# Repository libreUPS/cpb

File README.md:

# cpb
Communication panel board

In this repository you will find the `communication panel board` for the [libreUPS](https://github.com/libreUPS) complex.

Includes:
- can (x2)
- power bus (x2)
- LED (x3)
- button (x1)

Currently used in:
- bc1u15s

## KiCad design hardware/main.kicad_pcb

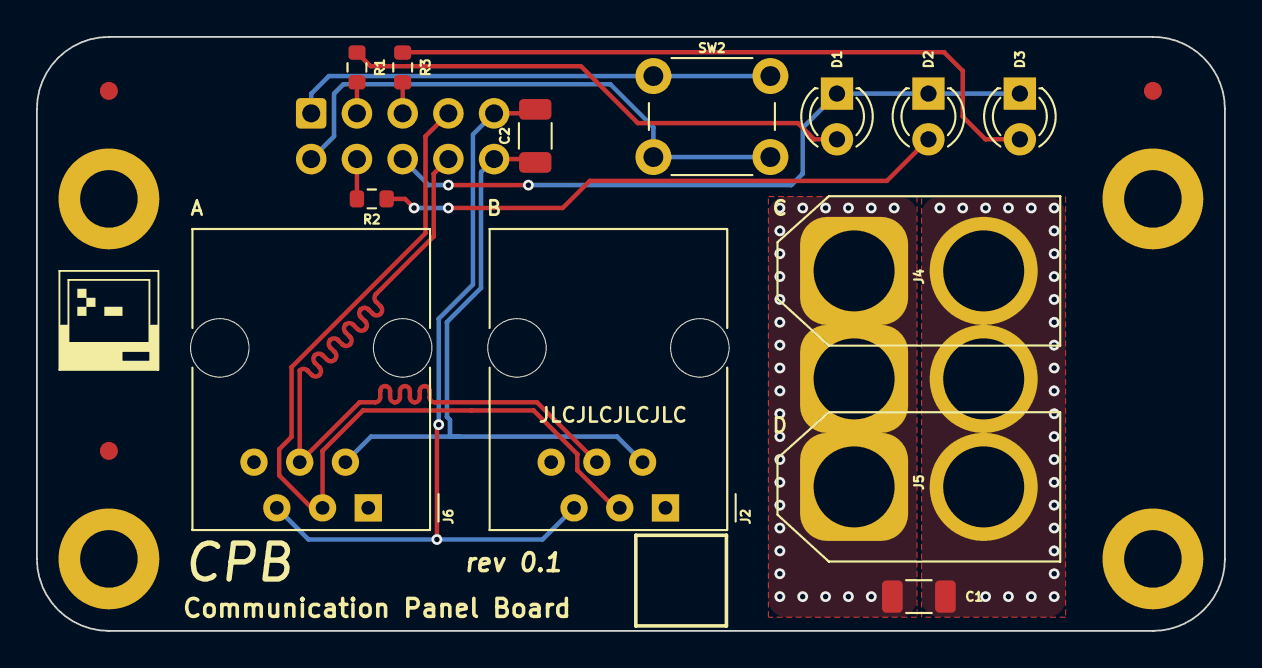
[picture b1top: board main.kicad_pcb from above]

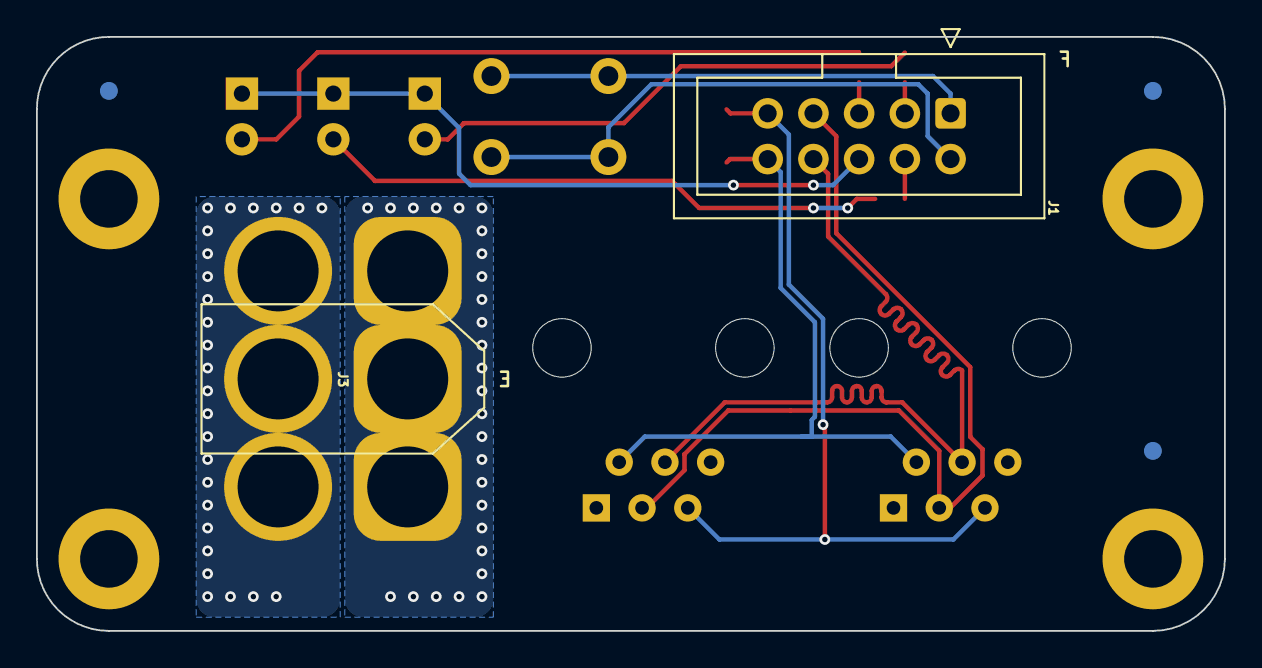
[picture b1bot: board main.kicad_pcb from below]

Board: 2 copper layers, 66.0 x 33.0 mm, 25 parts (5 on the bottom side), 15 nets.

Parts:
C1, C2: 100n; C_1206_3216Metric
D1: 204-10SUGD(E); LED_D3.0mm
D2: 204-10UYD(Y); LED_D3.0mm
D3: 204-10SURD(R); LED_D3.0mm
FID1, FID2, FID3, FID4, FID5, FID6: F; Fiducial_1mm_Mask3mm
H1, H2, H3, H4: H; MountingHole_3.2mm_M3_DIN965_Pad
J1: DS1013-10S; IDC-Header_2x05_P2.54mm_Vertical
J2, J6: KH-9752-6P6C; RJ12_Vertical
J3, J5: XT60; AMASS_XT60-F_1x02_P7.20mm_Vertical
J4: XT60; AMASS_XT60-M_1x02_P7.20mm_Vertical
R1, R2, R3: 1k; R_0603_1608Metric
SW2: TL1105HF160Q; SW_PUSH_6mm_H13mm

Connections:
/CANH: J1.7, J2.3, J6.3
/CANL: J1.8, J2.4, J6.4
/CANgnd: C2.2, J1.9, J2.5, J6.5
/CANvcc: C2.1, J1.10, J2.2, J6.2
/IO1: J1.3, R1.2
/IO2: J1.4, R2.2
/IO3: J1.5, R3.2
/K1: J1.1, SW2.1 (A)
/K2: J1.2, SW2.2 (B)
GND: D1.1 (K), D2.1 (K), D3.1 (K), J1.6
unnamed: C1.1, J3.1, J4.1, J5.1
unnamed: C1.2, J3.2, J4.2, J5.2
unnamed: D1.2 (A), R1.1
unnamed: D2.2 (A), R2.1
unnamed: D3.2 (A), R3.1

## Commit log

2023-06-24 init pcb
2023-06-24 finish pcb
